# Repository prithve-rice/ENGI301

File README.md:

<hl> ENGI301 </hl>
Repository for ENGI301 course work

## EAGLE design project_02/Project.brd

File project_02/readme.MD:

Directory for all Dexter board related files.
As all components are through-hole, bill of materials contains parts to be purchased and installed separately.

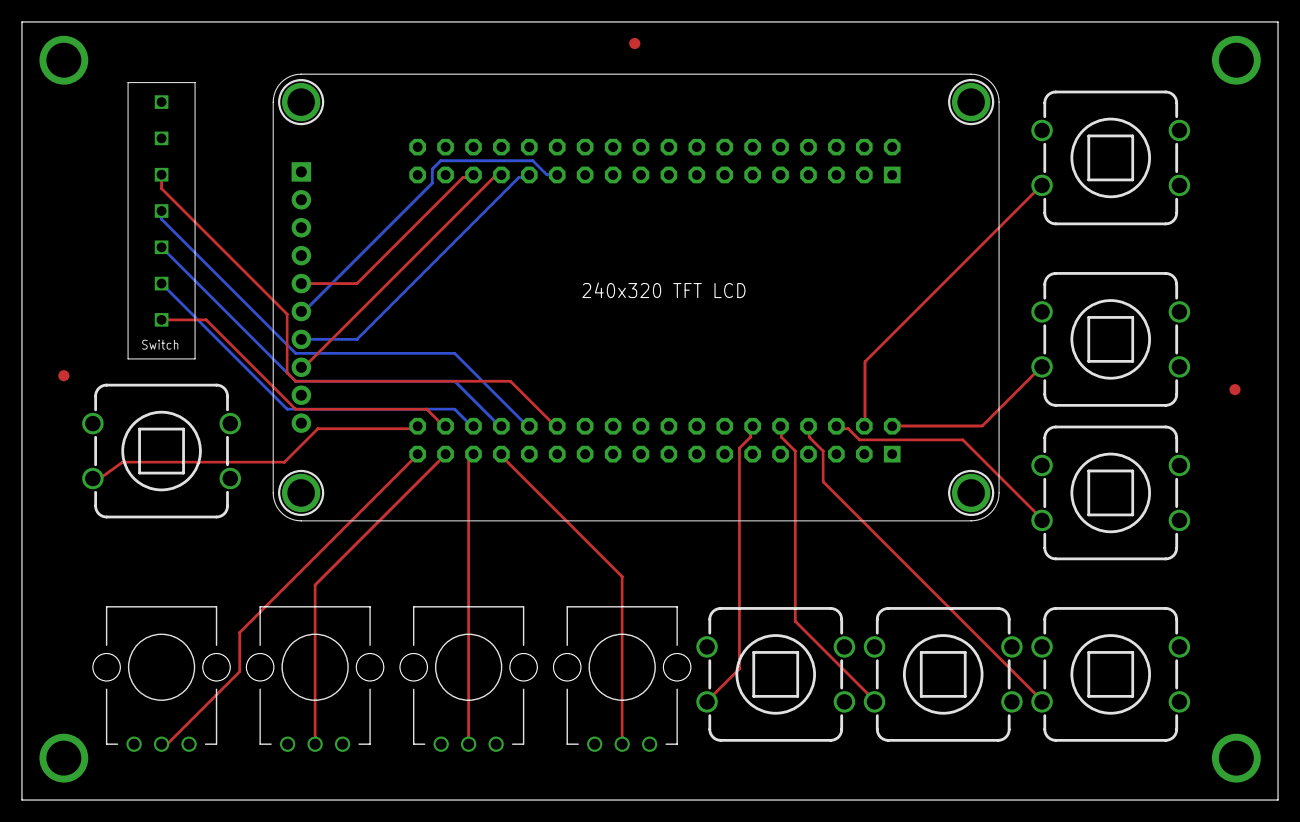
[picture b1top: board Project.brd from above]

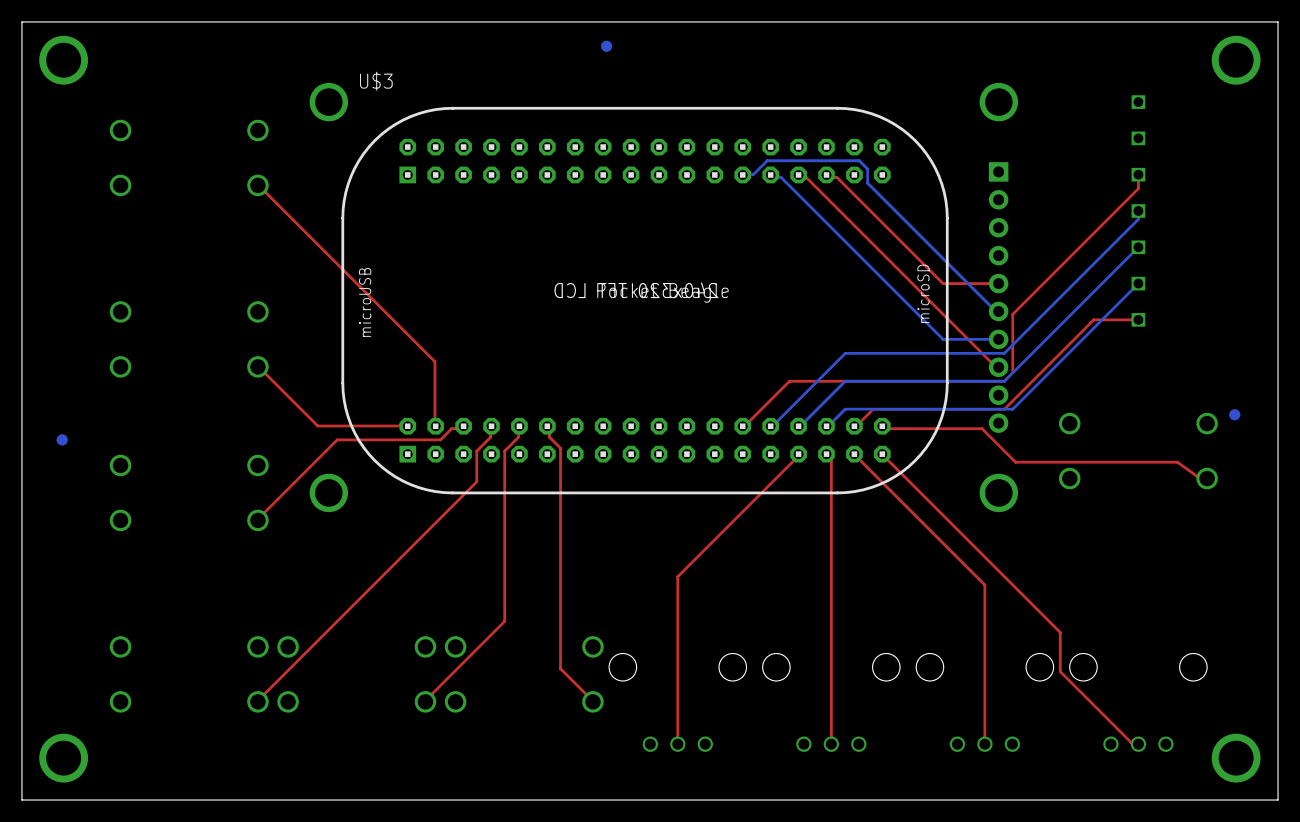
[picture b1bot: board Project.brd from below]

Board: 4 copper layers, 114.3 x 70.8 mm, 24 parts (4 on the bottom side), 15 nets.

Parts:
FUD1, FUD2, FUD3, FUD4, FUD5, FUD6: FIDUCIAL; FIDUCIAL_40MIL
MGT1, MGT2, MGT3, MGT4: MOUNTING_HOLE
R1, R2, R3, R4: PMETER; POT-PO90S
SW1, SW2, SW3, SW4, SW5, SW6, SW7: PUSH_BUTTON; BUTTON_12.5MM
U$1: SCREEN
U$2: SELECTOR_SWITCH
U$3: POCKETBEAGLE

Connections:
GND: R1.CW, R2.CW, R3.CW, R4.CW, SW1.4, SW2.4, SW3.4, SW4.4, SW5.4, SW6.4, SW7.4, U$1.1@JP1, U$2.P$2, U$3.15@P2
unnamed: U$2.P$3, U$3.26@P1
unnamed: U$2.P$4, U$3.28@P1
unnamed: U$2.P$5, U$3.30@P1
unnamed: U$2.P$6, U$3.32@P1
unnamed: R3.S, U$3.31@P1
unnamed: R2.S, U$3.33@P1
unnamed: R1.S, U$3.35@P1
unnamed: U$2.P$7, U$3.34@P1
unnamed: R4.S, U$3.29@P1
unnamed: U$1.6@JP1, U$3.25@P2
unnamed: U$1.7@JP1, U$3.27@P2
unnamed: U$1.8@JP1, U$3.29@P2
unnamed: U$1.5@JP1, U$3.31@P2
VDD_5V: R1.CCW, R2.CCW, R3.CCW, R4.CCW, SW1.2, SW2.2, SW3.2, SW4.2, SW5.2, SW6.2, SW7.2, U$1.2@JP1, U$2.P$1, U$3.2@P1, U$3.4@P1, U$3.6@P1, U$3.8@P1, U$3.10@P1, U$3.12@P1, U$3.13@P2, U$3.36@P1

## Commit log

2022-02-02 Updating README.md
2022-04-05 e301 and Porcupine folders for Dexter
    Dexter requires files outside of the e301 directory to function correctly - copying these two folders into the cloud9 directory should provide a functional Dexter.
    NOTE:
2022-04-05 Creating Porcupine folder
2022-04-05 Adding Porcupine Files
2022-04-05 Instructions to use the compiled C file
    Github isn't letting me upload the entire Porcupine engine
2022-05-07 reorg
2022-05-07 Rename readme.MD to porcupinereadme.MD
2022-05-08 Rename Project.brd to project_02/Project.brd
